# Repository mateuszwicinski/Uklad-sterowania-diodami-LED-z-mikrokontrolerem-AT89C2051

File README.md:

# Układ-sterowania-diodami-LED-z-mikrokontrolerem-AT89C2051 - Projekt PCB (Eagle)

Projekt wykonany w ramach laboratorium na Politechnice Gdańskiej.

**Opis projektu**
Zadanie polegało na odwzorowaniu udostępnionego schematu ideowego w środowisku **Autodesk Eagle** oraz samodzielnym zaprojektowaniu mozaiki ścieżek (**routing**) i rozmieszczeniu komponentów na płytce dwustronnej. Układ został przygotowany do fizycznej produkcji.

**Spis plików i ich zawartość**
* **WicinskiPI.sch** – Schemat ideowy układu (plik źródłowy Eagle).
* **WicinskiPI.brd** – Projekt obwodu drukowanego (plik źródłowy Eagle).
* **Wicinski.lbr** – Biblioteka z modelami elementów wykorzystanymi w projekcie.
* **Wydruk_schematu_2_1.pdf** – Schemat ideowy w formacie PDF do szybkiego podglądu.
* **Mozaika_1_1.pdf** – Widok ścieżek oraz otworów (mozaika) w formacie PDF.
* **Wicinski.pho** / **Wicinski_drl.pho** – Pliki Gerber zawierające dane o warstwach miedzi i otworach.
* **Wicinski.gpi** / **Wicinski_drl.dri** – Pliki raportów z procesu generowania plików produkcyjnych.
* **Netlista** – Wygenerowany spis wszystkich połączeń elektrycznych w układzie.

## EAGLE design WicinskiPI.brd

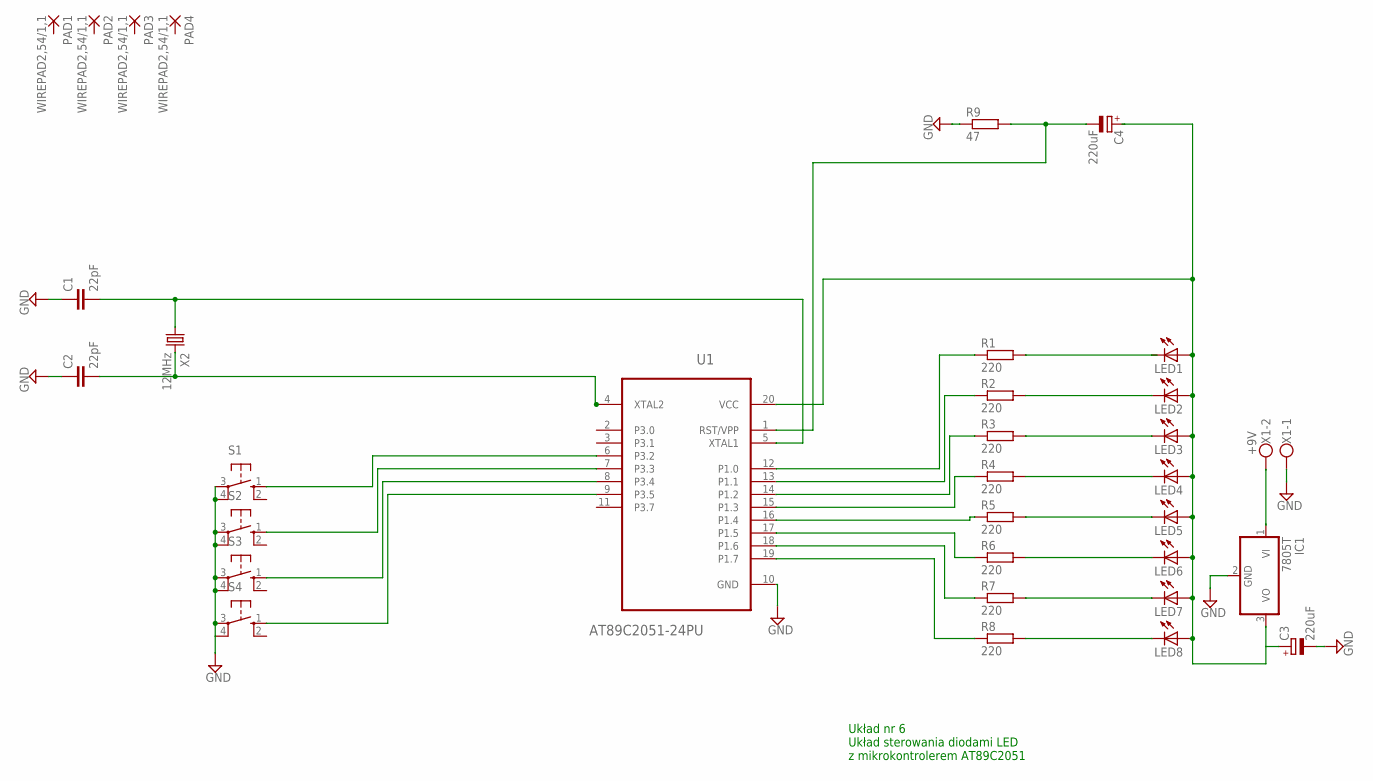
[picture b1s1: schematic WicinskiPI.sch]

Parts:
C1, C2: 22pF; C1206
C3, C4: 220uF; E3,5-8
IC1: 7805T; TO220H
LED1, LED2, LED3, LED4, LED5, LED6, LED7, LED8: LED3MM
PAD1, PAD2, PAD3, PAD4: WIREPAD2,54/1,1; 2,54/1,1
R1, R2, R3, R4, R5, R6, R7, R8: 220; R2012
R9: 47; R2012
S1, S2, S3, S4: 10-XX; B3F-10XX
U1: AT89C2051-24PU; DIP254P762X533-20
X1: +9V; W237-102
X2: 12MHz; HC49

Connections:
GND: C1.1, C2.1, C3.-, IC1.2 (GND), R9.1, S1.3, S1.4 (P1), S2.3, S2.4 (P1), S3.3, S3.4 (P1), S4.3, S4.4 (P1), U1.10 (GND), X1.1
unnamed: LED8.K (C), R8.2
unnamed: LED7.K (C), R7.2
unnamed: LED6.K (C), R6.2
unnamed: LED5.K (C), R5.2
unnamed: LED4.K (C), R4.2
unnamed: LED3.K (C), R3.2
unnamed: LED2.K (C), R2.2
unnamed: LED1.K (C), R1.2
unnamed: R1.1, U1.12 (P1.0)
unnamed: R2.1, U1.13 (P1.1)
unnamed: R3.1, U1.14 (P1.2)
unnamed: R4.1, U1.15 (P1.3)
unnamed: R5.1, U1.16 (P1.4)
unnamed: R6.1, U1.17 (P1.5)
unnamed: R7.1, U1.18 (P1.6)
unnamed: R8.1, U1.19 (P1.7)
unnamed: S1.1 (S), U1.6 (P3.2)
unnamed: S2.1 (S), U1.7 (P3.3)
unnamed: S3.1 (S), U1.8 (P3.4)
unnamed: S4.1 (S), U1.9 (P3.5)
unnamed: C1.2, U1.5 (XTAL1), X2.1
unnamed: C4.-, R9.2, U1.1 (RST/VPP)
unnamed: C2.2, U1.4 (XTAL2), X2.2
unnamed: IC1.1 (VI), X1.2
unnamed: C3.+, C4.+, IC1.3 (VO), LED1.A, LED2.A, LED3.A, LED4.A, LED5.A, LED6.A, LED7.A, LED8.A, U1.20 (VCC)

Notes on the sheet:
Układ nr 6 Układ sterowania diodami LED z mikrokontrolerem AT89C2051

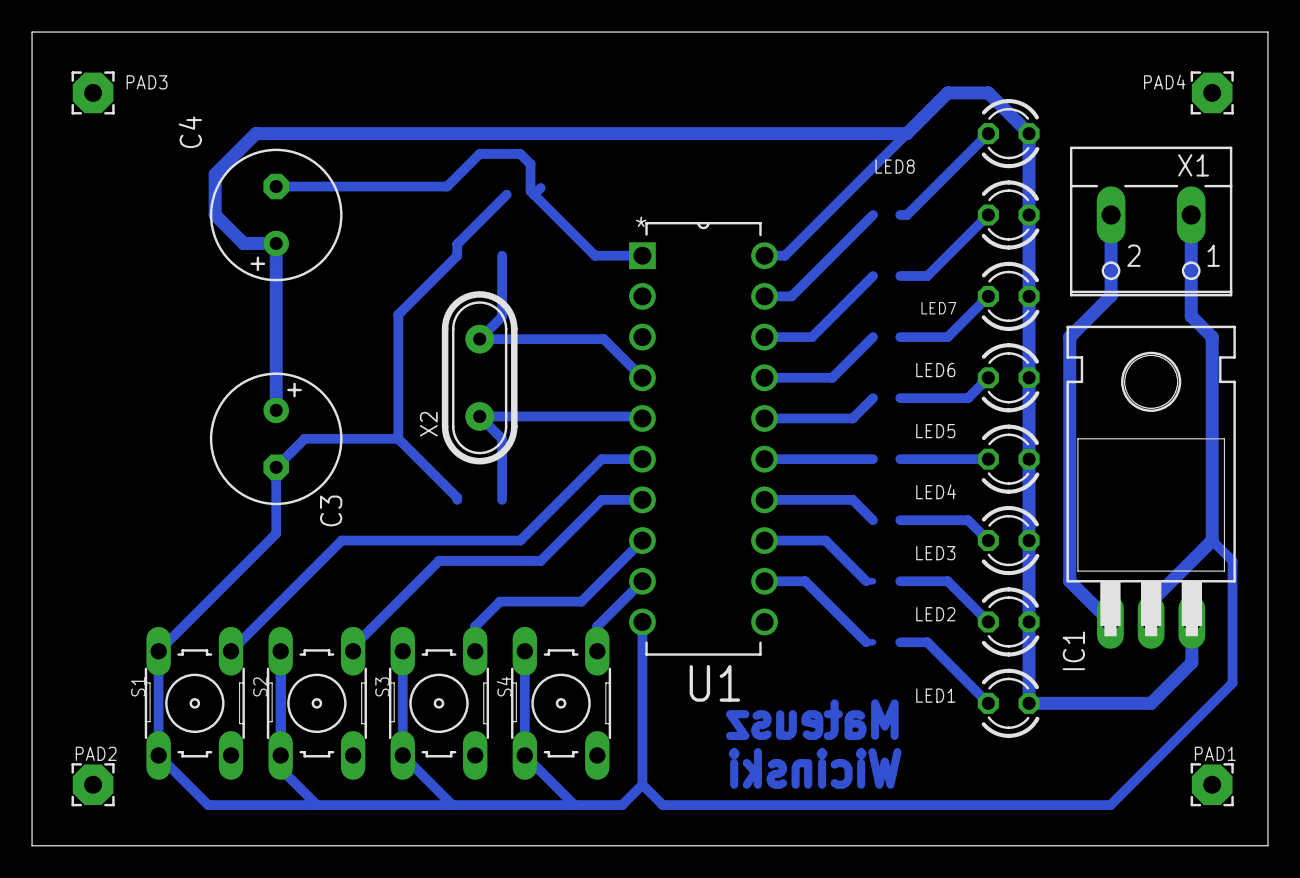
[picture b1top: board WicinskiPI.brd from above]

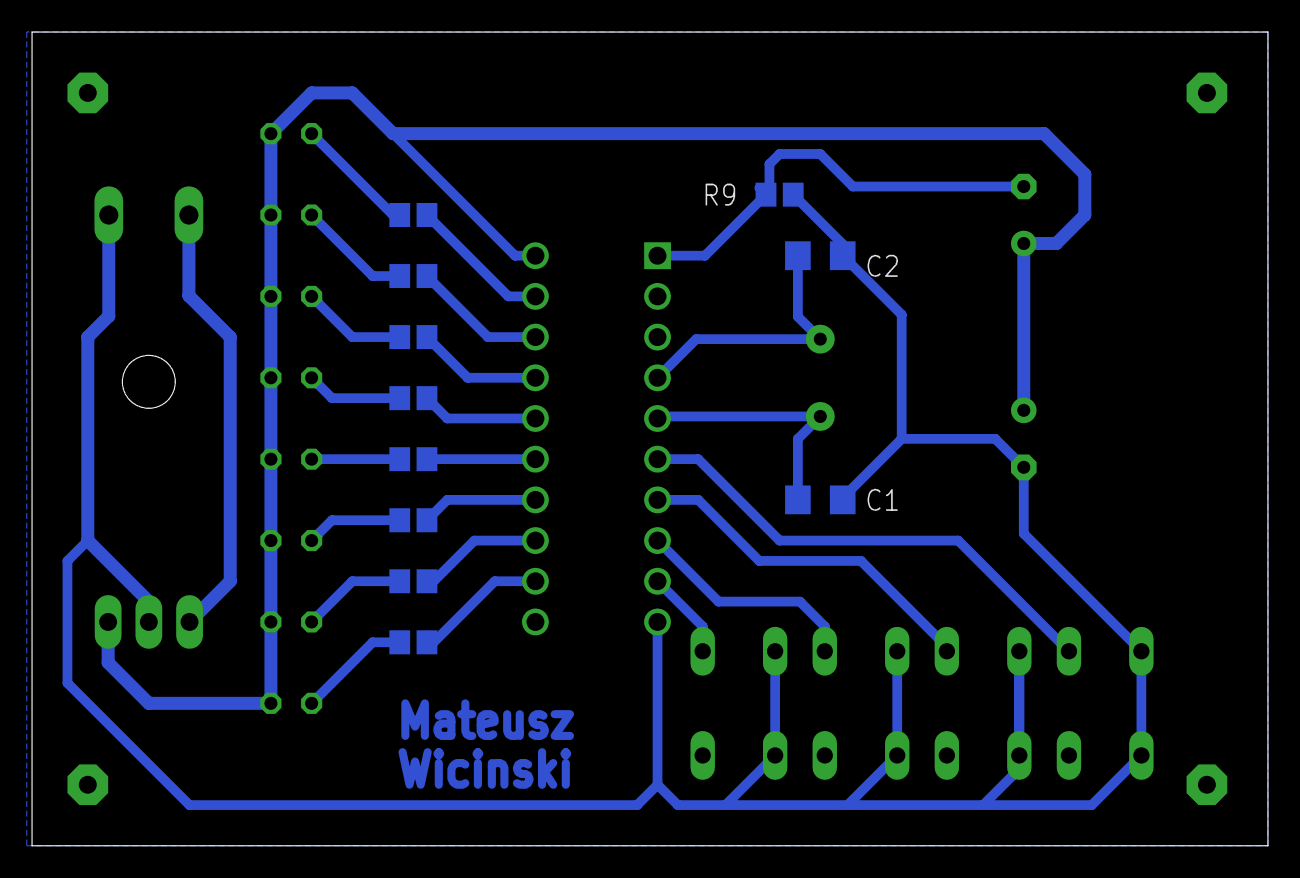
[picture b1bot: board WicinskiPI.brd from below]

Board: 2 copper layers, 77.1 x 50.8 mm, 33 parts (11 on the bottom side), 26 nets.

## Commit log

2026-04-27 Usuniecie straych plikow
